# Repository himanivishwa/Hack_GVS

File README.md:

## Bill of Materials (BOM)

| Qty | Component | Price (USD) | Price (INR) | Link |
|-----|-----------|--------------|--------------|------|
| 1 | 1uF Capacitor | $0.031 | ₹3 | [Link](https://quartzcomponents.com/products/50v-1uf-electrolytic-capacitor) |
| 5 | 01x02 5mm Screw Terminal | $0.066 | ₹6.32 | [Link](https://sharvielectronics.com/product/zb126-2-pin-screw-terminal-block-black-5mm-pitch/) |
| 2 | 10k Resistor | $0.084 | ₹8 | [Link](https://quartzcomponents.com/collections/all/products/10k-ohm-1-4-watt-resistor-with-1-tolerance-pack-of-10) |
| 1 | 550 Ohm Resistor | $0.084 | ₹8 | [Link](https://quartzcomponents.com/products/560-ohm-1-4-watt-resistor-with-1-tolerance-pack-of-10) |
| 1 | 100k Resistor | $0.094 | ₹9 | [Link](https://quartzcomponents.com/collections/all/products/100k-ohm-1-4-watt-resistor-with-1-tolerance-pack-of-10) |
| 1 | TL082 Op-Amp | $0.42 | ₹39.63 | [Link](https://sharvielectronics.com/product/tl082-jfet-input-operational-amplifier-ic-dip-8-package/) |
| 2 | 9V Battery | – | – | – |
| 8 | 1.5V Cell | – | – | – |
| 1 | Microcontroller (Pico RP2040) | $4.88 | ₹465.79 | [Link](https://sharvielectronics.com/product/raspberry-pi-pico-rp2040-pre-soldered-headers/) |
| 2 | 9V Battery Holder | $0.27 | ₹25.45 | [Link](https://sharvielectronics.com/product/9v-battery-holder-without-cover/) |
| 2 | 4xAAA Holder | $0.5 | ₹48 | [Link](https://sharvielectronics.com/product/battery-holder-4xaaa/) |
| 1 | PCB | $2 | ₹190.77 | [Link](https://jlcpcb.com/) |
| – | E-post PCB Shipping | $7.71 | ₹735.42 | – |
| – | Quartz Shipping | $0.52 | ₹50 | – |
| – | Quartz Tax | $0.16 | ₹15.66 | – |
| – | Sharvielect IGST (18%) | $1.39 | ₹132.71 | – |
| – | Sharvielect Shipping | $0.89 | ₹85 | – |
| **Total** | | **19.11** | **₹1822.75** | |

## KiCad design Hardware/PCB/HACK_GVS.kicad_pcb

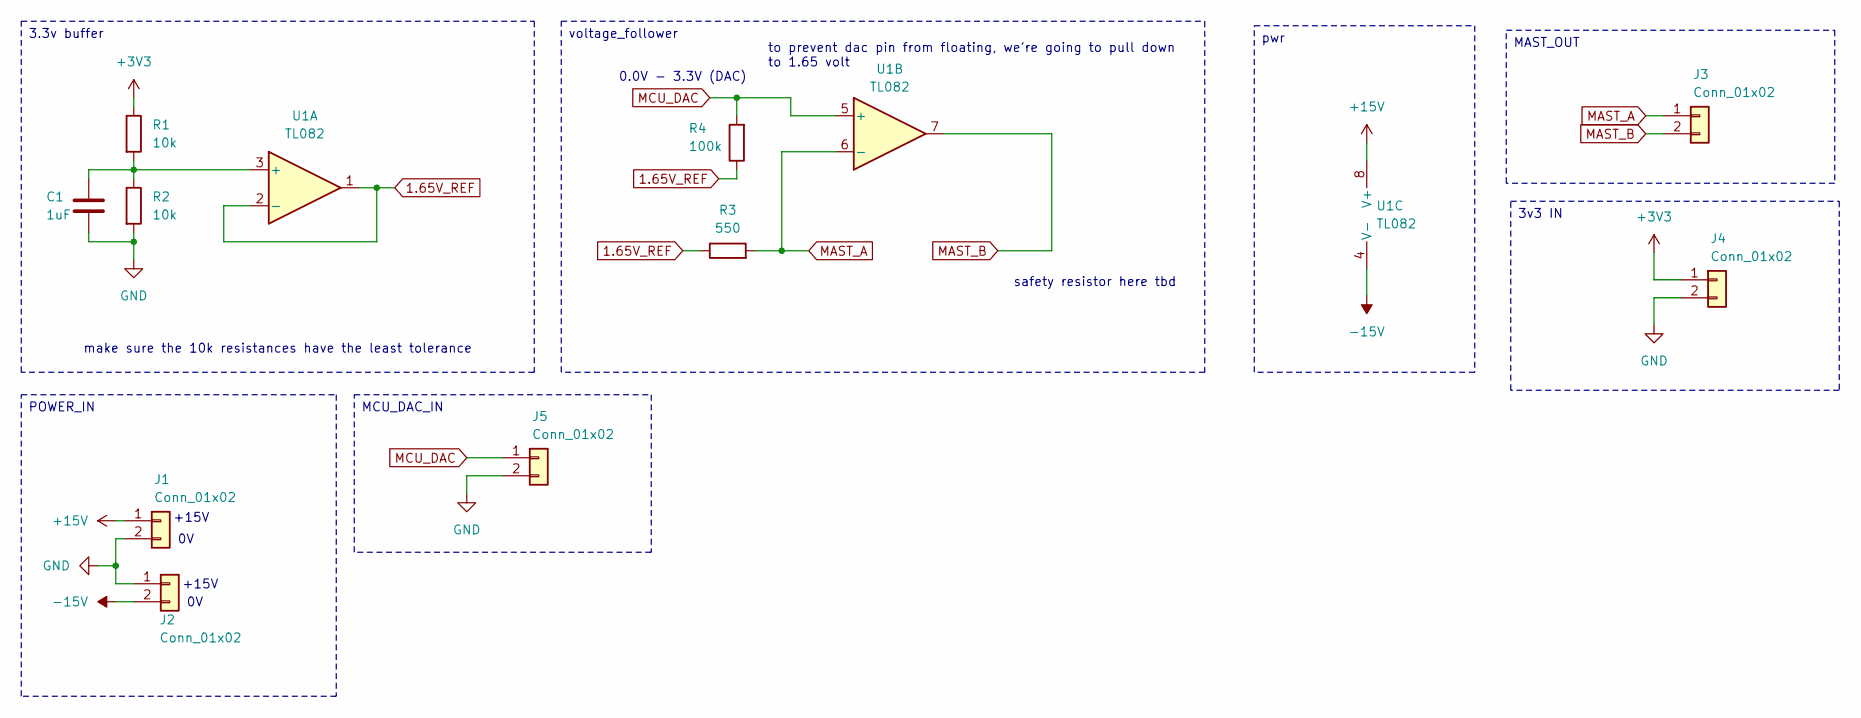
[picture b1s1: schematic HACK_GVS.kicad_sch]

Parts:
C1: 1uF; C_Disc_D3.8mm_W2.6mm_P2.50mm
J1, J2, J3, J4, J5: Conn_01x02; TerminalBlock_MaiXu_MX126-5.0-02P_1x02_P5.00mm_step
R1, R2: 10k; R_Axial_DIN0204_L3.6mm_D1.6mm_P5.08mm_Horizontal
R3: 550; R_Axial_DIN0204_L3.6mm_D1.6mm_P5.08mm_Horizontal
R4: 100k; R_Axial_DIN0204_L3.6mm_D1.6mm_P5.08mm_Horizontal
U1: TL082; DIP-8_W7.62mm_LongPads

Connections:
1.65V_REF: R3.1, R4.1, U1.1, U1.2 (-)
+3V3: J4.1, R1.1
+15V: J1.1, U1.8 (V+)
-15V: J2.2, U1.4 (V-)
GND: C1.2, J1.2, J2.1, J4.2, J5.2, R2.2
MAST_A: J3.1, R3.2, U1.6 (-)
MAST_B: J3.2, U1.7
MCU_DAC: J5.1, R4.2, U1.5 (+)
unnamed: C1.1, R1.2, R2.1, U1.3 (+)

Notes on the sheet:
0.0V - 3.3V (DAC)
+15V
make sure the 10k resistances have the least tolerance
to prevent dac pin from floating, we're going to pull down to 1.65 volt
safety resistor here tbd
POWER_IN
MAST_OUT
MCU_DAC_IN
pwr
3v3 IN
voltage_follower
3.3v buffer

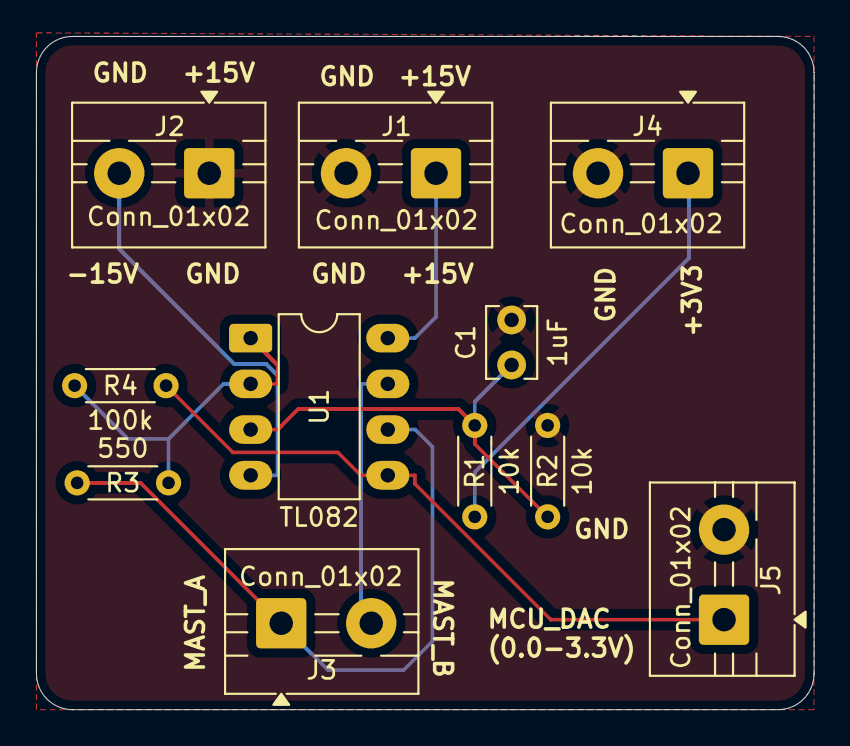
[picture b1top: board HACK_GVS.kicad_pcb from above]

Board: 2 copper layers, 43.2 x 37.4 mm, 11 parts (0 on the bottom side), 9 nets.
